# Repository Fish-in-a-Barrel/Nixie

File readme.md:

# Yet Another Nixie Clock

https://github.com/user-attachments/assets/0fcae77a-54a8-4b7d-9e90-6edd31807fbd

## Introduction

This is my Nixie clock project. It was created as an excuse to learn more about electronics and it touches on power circuits, microcontrollers, serial communications, and more.

The clock runs 12 IN-12A Nixie tubes that display the time and date. INS-1 tubes are used for digit separators. It also includes:
- USB-C PD power input
- Boost converter to provide 180V for the nixie tubes
- GPS module for date/time synchronization
- User-selectable timezone
- RTC module for precision timekeeping, and power-off timekeeping
- 128x32 mono OLED display for diagnostics
- Rotary encoder for user input
- I2C Driver boards for each tube

## Development Tools
**Hardware**: KiCad 8
**Firmware**: MPLAB X IDE

## Architecture

### Main Processor
A [Microchip PIC16F15224](https://ww1.microchip.com/downloads/aemDocuments/documents/MCU08/ProductDocuments/DataSheets/PIC16F15213-14-23-24-43-44-Microcontroller-Data-Sheet-40002195.pdf) 8-bit microcontroller is the main processing unit of the clock. It controls the boost converter while managing and coordinating the other hardware modules.

### Power

A [Diodes Incorporated AP33772](https://www.diodes.com/assets/Datasheets/products_inactive_data/AP33772.pdf) is used to negotiate with a PD source for the input power. The AP33772 is controlled by the main MCU via I2C. The AP33772 requests 12V from the power source, which supplies the boost converter.

The AP33772 also provides a dedicated 5V power source. This is a low current source, so it is only used to drive the MCU and UI, which are needed during power-up. A separate 78L05 regulator (powered by the 12V from USB VBUS) provides 5V power to all of the other devices.

Finally, the AP33772 provides over-current and over-voltage protection features.

### User Interface
A 128x32 OLED display (driven by an [SSD1306](https://cdn-shop.adafruit.com/datasheets/SSD1306.pdf)) is used to display status and diagnostics information. A rotary encoder with detent is used to scroll through the different display pages, and to select timezone and DST support. The OLED pixel data is sent over I2C.

### Real Time Clock
A [DS3231](https://www.analog.com/media/en/technical-documentation/data-sheets/ds3231.pdf) RTC module provides an accurate time source for the clock. It is the source of the time/date displayed and is only updated if it differs from the GPS time. The RTC module is also equiped with a battery backup. This allows the clock to display time/date immediately after power-on instead of having to wait several minutes for valid GPS data. RTC data is sent over I2C.

### GPS
The [U-Blox NEO-6M](https://content.u-blox.com/sites/default/files/products/documents/NEO-6_DataSheet_%28GPS.G6-HW-09005%29.pdf) GPS module provides a reference time to initialize the RTC. The module streams standard NMEA messages to the primary MCU over UART serial. Time/date are decoded from these messages.

### Nixie Drivers
Each Nixie tube has a driver board. This board has a [Microchip PIC16F15243](https://ww1.microchip.com/downloads/aemDocuments/documents/MCU08/ProductDocuments/DataSheets/PIC16F15213-14-23-24-43-44-Microcontroller-Data-Sheet-40002195.pdf) MCU in I2C client mode receiving commands from the primary MCU. This client MCU drives the Nixie pins and provides features such as digit cross-fading and cathode maintenance.

## Project Components

### ClockController

This is the main controller board. It connects to a header on the back of the display board and has these main components:
- Primary MCU
- USB PD components
- Boost converter circuitry
- User Interface

### Hardware / Display Board

This board servers as the main support structure of the clock. The Nixie drivers connect to headers on the front of the board. The controller board, GPS, and RTC all connect to the back of the board.

### NixieDriver

The driver board for each individual IN-12 Nixie tube.

### NixieDriverTester

This is a stand-alone test board that will power and exercise a single NixieDriver and tube. It is used for QA of assembled driver boards and testing of the NixieDriver firmware.

### Hardware / Nixie Driver ICSP Adapter

A small board that attaches to a NixieDriver and provides a pin-out compatible with a PICKIT 5 programmer for In Circuit Serial Programming.

### Hardware / Separator

A tiny board that adapts the physical interface of the INS-1 tubes used as digit separators.

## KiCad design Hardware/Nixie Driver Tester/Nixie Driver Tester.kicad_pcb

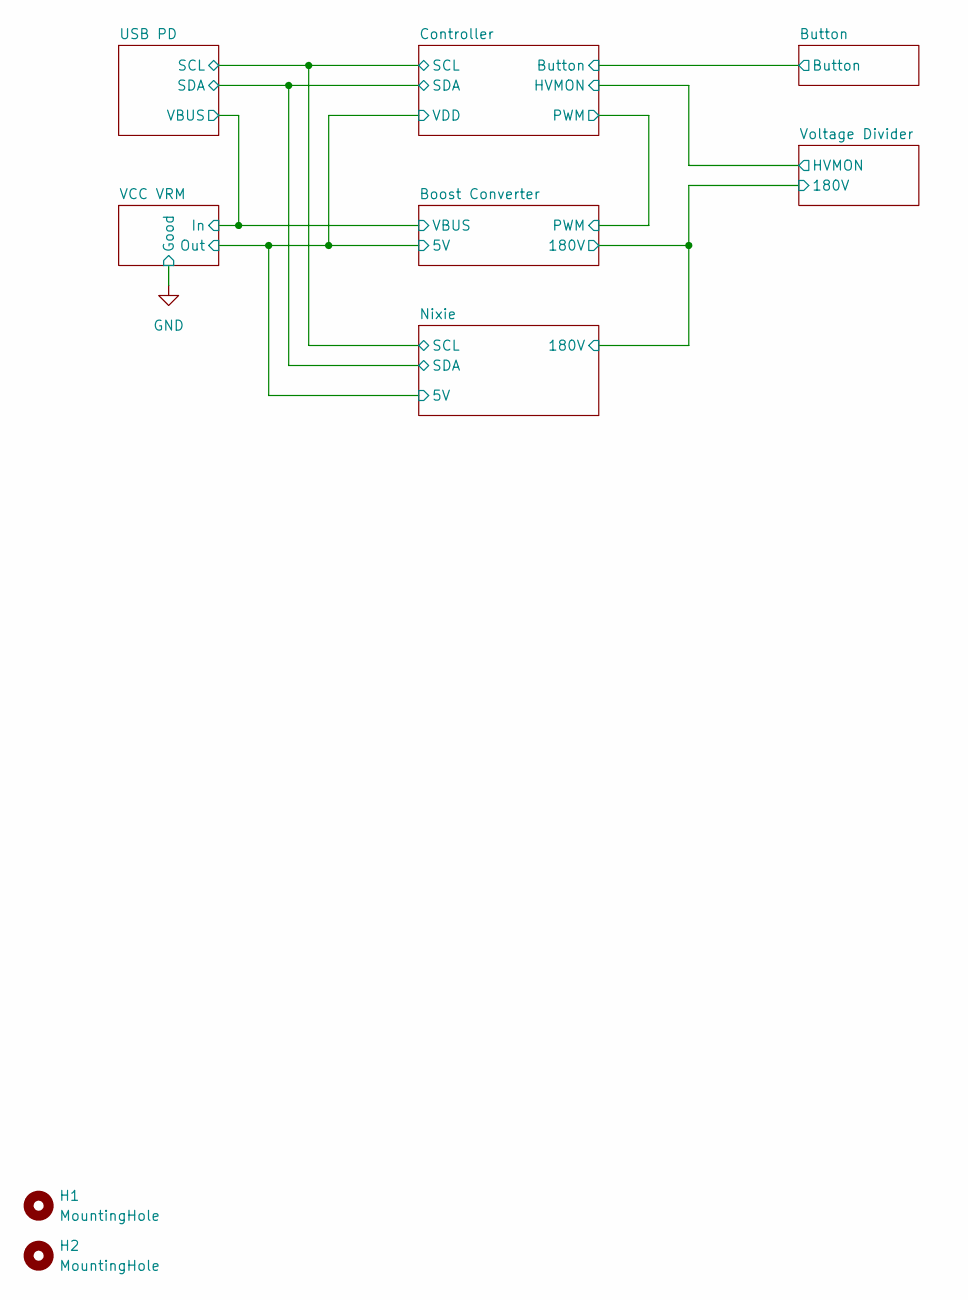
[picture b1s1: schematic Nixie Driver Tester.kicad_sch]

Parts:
H1, H2: MountingHole; MountingHole_3.2mm_M3

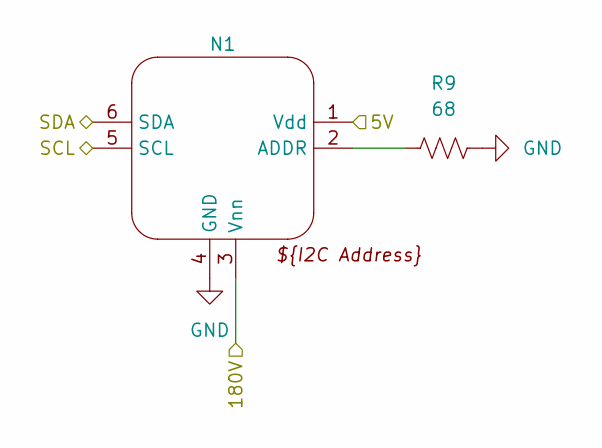
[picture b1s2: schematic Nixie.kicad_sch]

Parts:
N1: Nixie; Nixie Driver V2
R9: 68; R_1206_3216Metric

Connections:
/Boost Converter/180V: N1.3 (Vnn); also elsewhere on the board
/Controller/SCL: N1.5 (SCL); also elsewhere on the board
/Controller/SDA: N1.6 (SDA); also elsewhere on the board
/VCC VRM/V_Out: N1.1 (Vdd); also elsewhere on the board
GND: N1.4 (GND), R9.2; also elsewhere on the board
unnamed: N1.2 (ADDR), R9.1

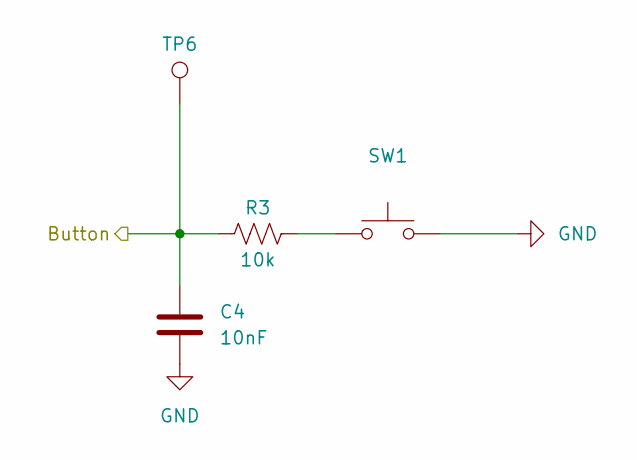
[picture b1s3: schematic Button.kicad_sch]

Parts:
C4: 10nF; C_0603_1608Metric
R3: 10k; R_0603_1608Metric
SW1: SW_Omron_B3FS; B3F-10xx
TP6: BTN; TestPoint_Keystone_5015_Micro_Mini

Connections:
/Button/Button: C4.1, R3.1, TP6.1 (1_1); also elsewhere on the board
GND: C4.2, SW1.2; also elsewhere on the board
unnamed: R3.2, SW1.1

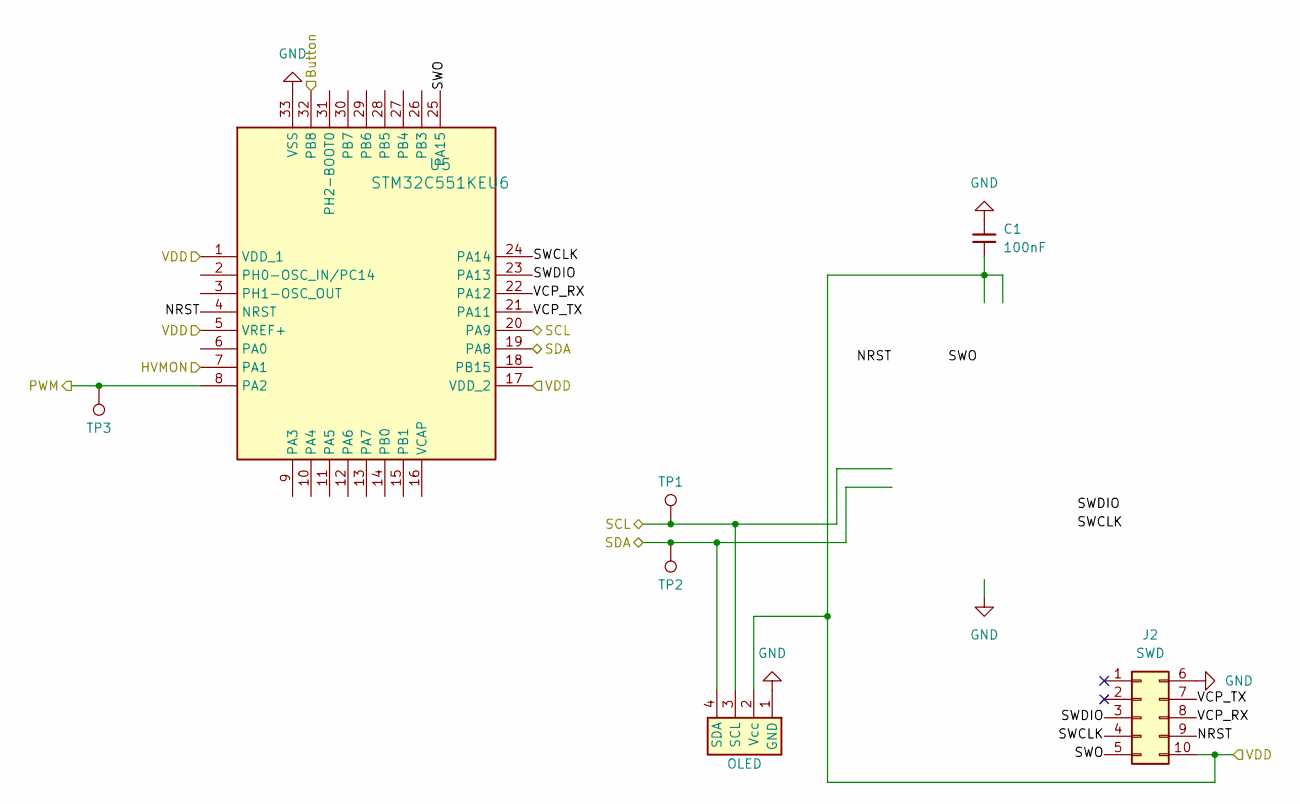
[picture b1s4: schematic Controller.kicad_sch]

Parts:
C1: 100nF; C_0603_1608Metric
J1: OLED; SSD1306 0.91 128x32 OLED
J2: SWD; AVX-009159010061911
TP1: SCL; TestPoint_Keystone_5015_Micro_Mini
TP2: SDA; TestPoint_Keystone_5015_Micro_Mini
TP3: PWM; TestPoint_Keystone_5015_Micro_Mini
U5: STM32C551KEU6; UFQFPN-32-1EP_5x5mm_P0.5mm_EP3.5x3.5mm; Manufacturer_Part_Number STM32C551KEU6

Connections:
/Boost Converter/PWM: TP3.1 (1_1), U5.8 (PA2); also elsewhere on the board
/Button/Button: U5.32 (PB8); also elsewhere on the board
/Controller/HVMON: U5.7 (PA1); also elsewhere on the board
/Controller/NRST: J2.9, U5.4 (NRST)
/Controller/SCL: J1.3 (SCL), TP1.1 (1_1), U5.20 (PA9); also elsewhere on the board
/Controller/SDA: J1.4 (SDA), TP2.1 (1_1), U5.19 (PA8); also elsewhere on the board
/Controller/SWCLK: J2.4, U5.24 (PA14)
/Controller/SWDIO: J2.3, U5.23 (PA13)
/Controller/SWO: J2.5, U5.25 (PA15)
/Controller/VCP_RX: J2.8, U5.22 (PA12)
/Controller/VCP_TX: J2.7, U5.21 (PA11)
/VCC VRM/V_Out: C1.2, J1.2 (Vcc), J2.10, U5.1 (VDD_1), U5.5 (VREF+), U5.17 (VDD_2); also elsewhere on the board
GND: C1.1, J1.1 (GND), J2.6, U5.33 (VSS); also elsewhere on the board

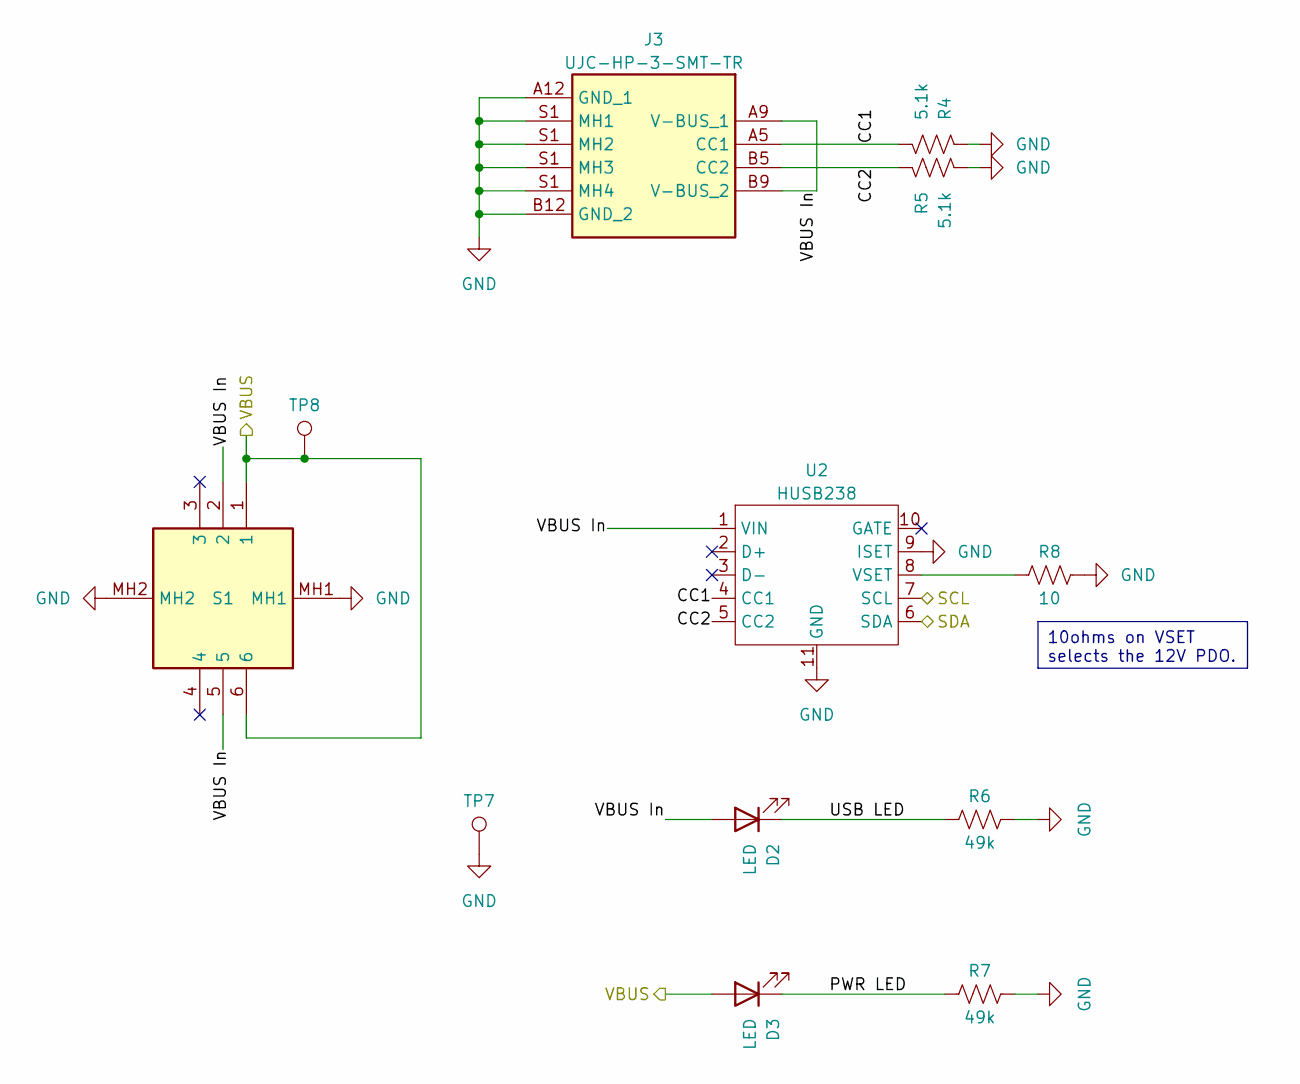
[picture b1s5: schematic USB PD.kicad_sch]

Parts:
D2, D3: LED; LED_0603_1608Metric
J3: UJC-HP-3-SMT-TR; CUI_UJC-HP-3-SMT-TR; Manufacturer_Part_Number UJC-HP-3-SMT-TR; Mouser Part Number 490-UJC-HP-3-SMT-TR
R4, R5: 5.1k; R_0603_1608Metric
R6, R7: 49k; R_0603_1608Metric
R8: 10; R_0603_1608Metric
S1: SLW-111629-7A-D; SLW1116297AD; Mouser Part Number 179-SLW-111629-7A-D
TP7: GND; TestPoint_Keystone_5015_Micro_Mini
TP8: VBUS; TestPoint_Keystone_5015_Micro_Mini
U2: HUSB238; DFN-10-1EP_3x3mm_P0.5mm_EP1.65x2.38mm

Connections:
/Boost Converter/VBUS: D3.2 (A), S1.1, S1.6, TP8.1 (1_1); also elsewhere on the board
/Controller/SCL: U2.7 (SCL); also elsewhere on the board
/Controller/SDA: U2.6 (SDA); also elsewhere on the board
/USB PD/CC1: J3.A5 (CC1), R4.2, U2.4 (CC1)
/USB PD/CC2: J3.B5 (CC2), R5.1, U2.5 (CC2)
/USB PD/PWR LED: D3.1 (K), R7.1
/USB PD/USB LED: D2.1 (K), R6.1
/USB PD/VBUS In: D2.2 (A), J3.A9 (V-BUS_1), J3.B9 (V-BUS_2), S1.2, S1.5, U2.1 (VIN)
GND: J3.A12 (GND_1), J3.B12 (GND_2), J3.S1 (MH3), R4.1, R5.2, R6.2, R7.2, R8.2, S1.MH1, S1.MH2, TP7.1 (1_1), U2.9 (ISET), U2.11 (GND); also elsewhere on the board
unnamed: R8.1, U2.8 (VSET)

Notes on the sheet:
10ohms on VSET selects the 12V PDO.

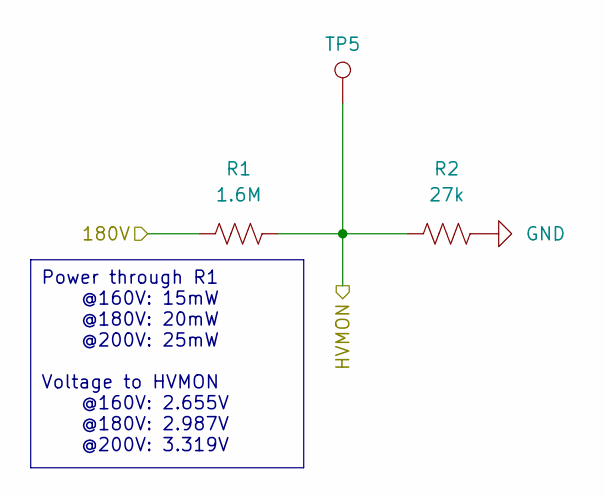
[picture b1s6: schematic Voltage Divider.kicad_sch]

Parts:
R1: 1.6M; R_1206_3216Metric
R2: 27k; R_1206_3216Metric
TP5: MON; TestPoint_Keystone_5015_Micro_Mini

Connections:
/Boost Converter/180V: R1.1; also elsewhere on the board
/Controller/HVMON: R1.2, R2.1, TP5.1 (1_1); also elsewhere on the board
GND: R2.2; also elsewhere on the board

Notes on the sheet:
Power through R1 @160V: 15mW @180V: 20mW @200V: 25mW Voltage to HVMON @160V: 2.655V @180V: 2.987V @200V: 3.319V

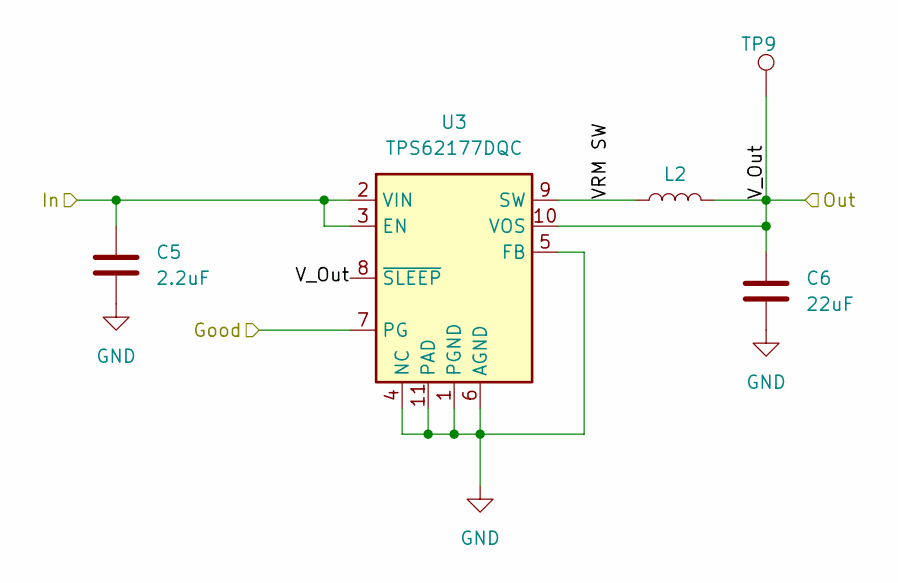
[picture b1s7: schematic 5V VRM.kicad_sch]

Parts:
C5: 2.2uF; C_0805_2012Metric
C6: 22uF; C_0805_2012Metric
L2: VLS4012CX-100M-1; TDK LPS40xx
TP9: 3.3V; TestPoint_Keystone_5015_Micro_Mini
U3: TPS62177DQC; WSON-10-1EP_2x3mm_P0.5mm_EP0.84x2.4mm_ThermalVias

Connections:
/Boost Converter/VBUS: C5.1, U3.2 (VIN), U3.3 (EN); also elsewhere on the board
/VCC VRM/VRM SW: L2.1, U3.9 (SW)
/VCC VRM/V_Out: C6.1, L2.2, TP9.1 (1_1), U3.8 (~SLEEP), U3.10 (VOS); also elsewhere on the board
GND: C5.2, C6.2, U3.1 (PGND), U3.4 (NC), U3.5 (FB), U3.6 (AGND), U3.7 (PG), U3.11 (PAD); also elsewhere on the board

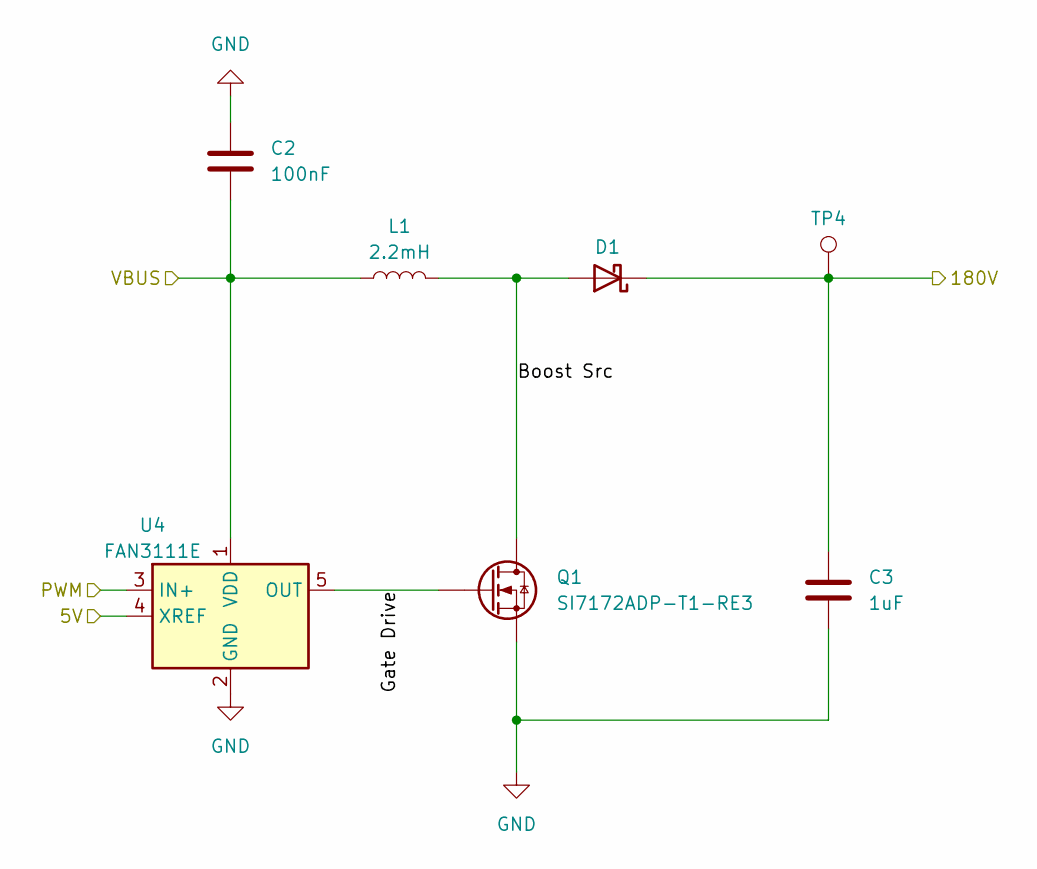
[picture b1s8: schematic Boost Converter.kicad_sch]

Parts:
C2: 100nF; C_0805_2012Metric
C3: 1uF; R_1812_4532Metric
D1: SMD220PL-TP; D_SOD-123
L1: 2.2mH; L_Wuerth_WE-PD-Typ-LS
Q1: SI7172ADP-T1-RE3; PowerPAK_SO-8_Single
TP4: VNN; TestPoint_Keystone_5015_Micro_Mini
U4: FAN3111E; SOT-23-5

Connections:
/Boost Converter/180V: C3.1, D1.1 (K), TP4.1 (1_1); also elsewhere on the board
/Boost Converter/Boost Src: D1.2 (A), L1.2, Q1.D
/Boost Converter/Gate Drive: Q1.G, U4.5 (OUT)
/Boost Converter/PWM: U4.3 (IN+); also elsewhere on the board
/Boost Converter/VBUS: C2.2, L1.1, U4.1 (VDD); also elsewhere on the board
/VCC VRM/V_Out: U4.4 (XREF); also elsewhere on the board
GND: C2.1, C3.2, Q1.S, U4.2 (GND); also elsewhere on the board

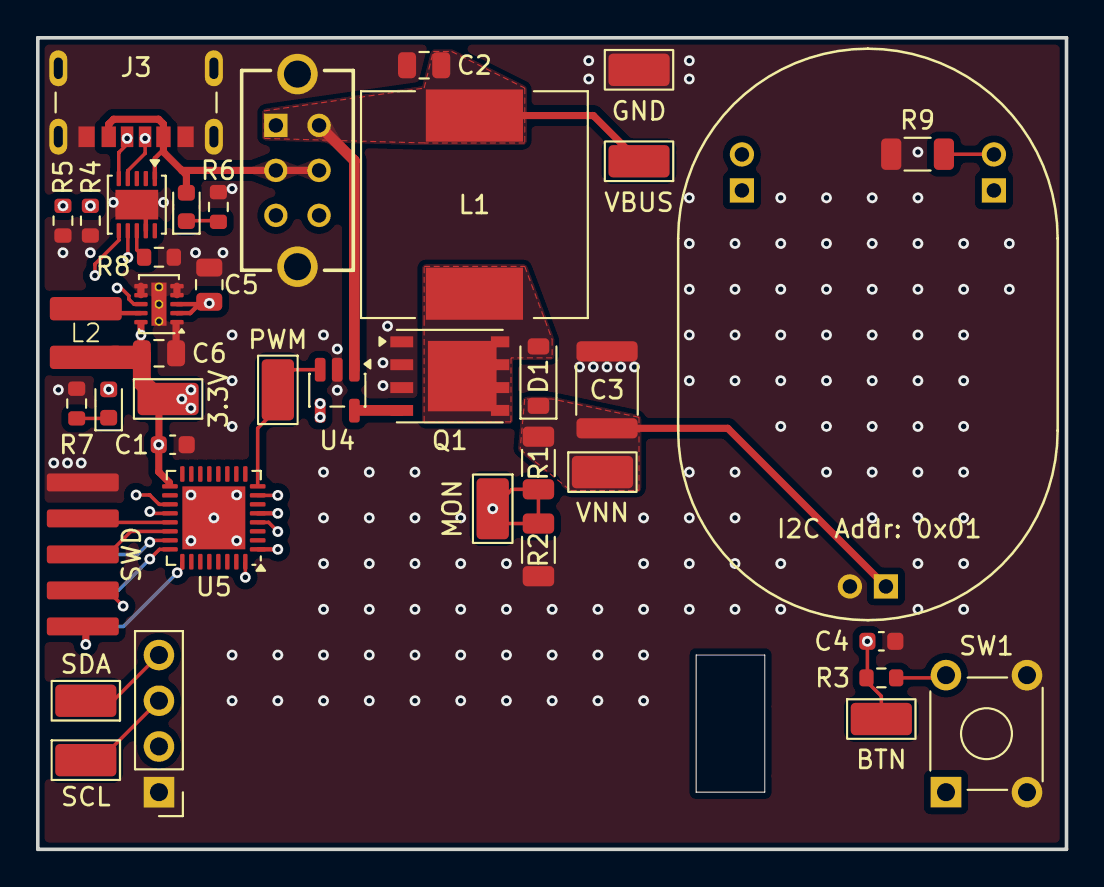
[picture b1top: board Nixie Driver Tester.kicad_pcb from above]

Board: 4 copper layers, 57.1 x 45.1 mm, 42 parts (1 on the bottom side), 26 nets.

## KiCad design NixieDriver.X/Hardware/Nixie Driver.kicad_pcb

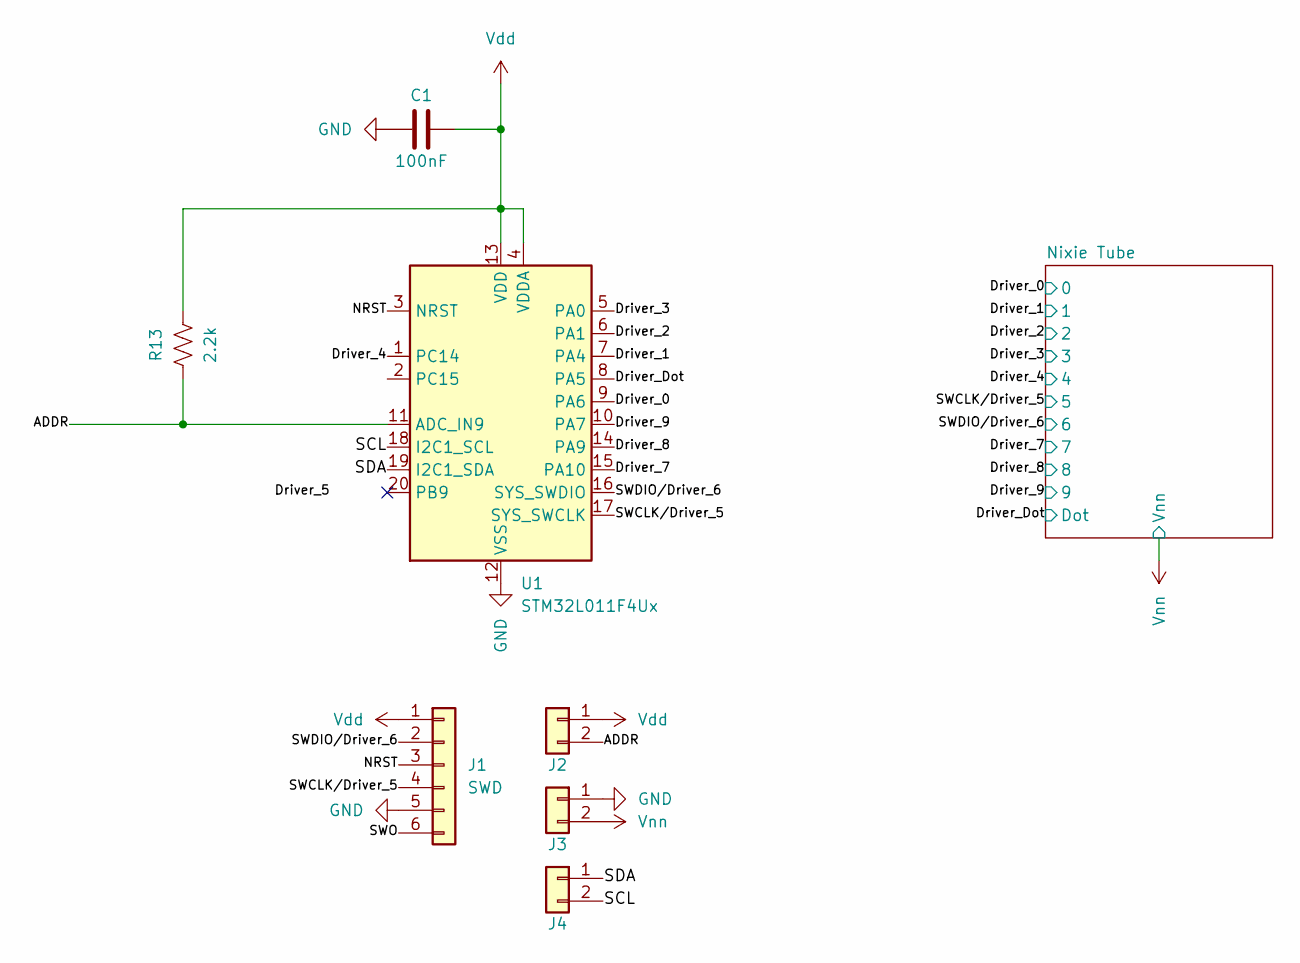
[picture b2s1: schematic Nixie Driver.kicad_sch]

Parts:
C1: 100nF; C_0603_1608Metric
J1: SWD; Tag-Connect EVC3-06
J2, J3, J4: Conn_01x03; PinHeader_1x02_P2.00mm_Vertical
R13: 2.2k; R_0603_1608Metric
U1: STM32L011F4Ux; ST_UFQFPN-20_3x3mm_P0.5mm

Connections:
/ADDR: J2.2, R13.1, U1.11 (ADC_IN9)
/Driver_0: U1.9 (PA6); also elsewhere on the board
/Driver_1: U1.7 (PA4); also elsewhere on the board
/Driver_2: U1.6 (PA1); also elsewhere on the board
/Driver_3: U1.5 (PA0); also elsewhere on the board
/Driver_4: U1.1 (PC14); also elsewhere on the board
/Driver_7: U1.15 (PA10); also elsewhere on the board
/Driver_8: U1.14 (PA9); also elsewhere on the board
/Driver_9: U1.10 (PA7); also elsewhere on the board
/Driver_Dot: U1.8 (PA5); also elsewhere on the board
/NRST: J1.3, U1.3 (NRST)
/SCL: J4.2, U1.18 (I2C1_SCL)
/SDA: J4.1, U1.19 (I2C1_SDA)
/SWCLK/Driver_5: J1.4, U1.17 (SYS_SWCLK); also elsewhere on the board
/SWDIO/Driver_6: J1.2, U1.16 (SYS_SWDIO); also elsewhere on the board
/SWO: J1.6
GND: C1.2, J1.5, J3.1, U1.12 (VSS); also elsewhere on the board
Vdd: C1.1, J1.1, J2.1, R13.2, U1.4 (VDDA), U1.13 (VDD)
Vnn: J3.2; also elsewhere on the board

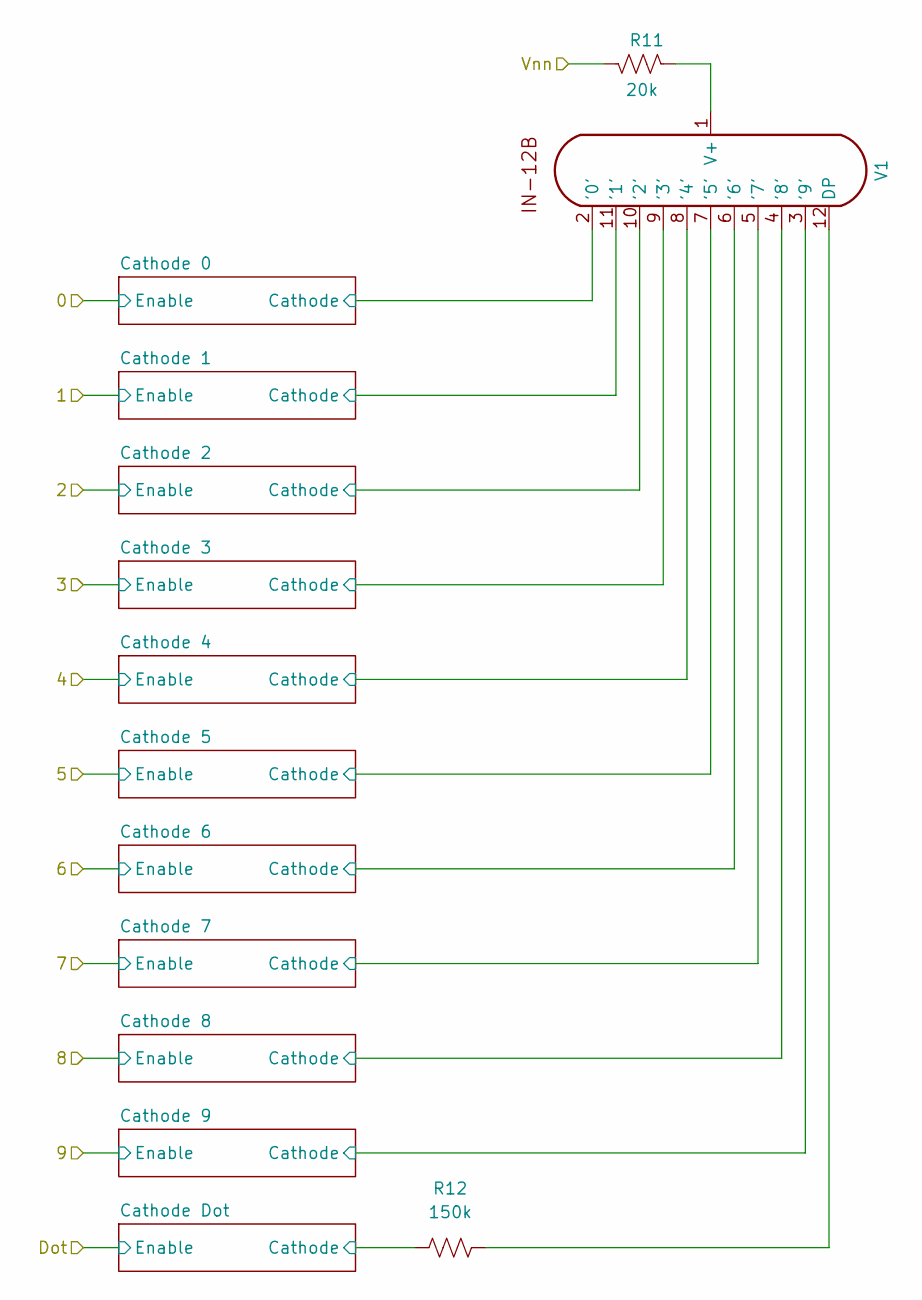
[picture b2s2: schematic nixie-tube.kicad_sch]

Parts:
R11: 20k; R_1206_3216Metric
R12: 150k; R_0805_2012Metric
V1: IN-12B; IN-12[A_B] with center hole

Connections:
/Nixie Tube/Cathode 0/Cathode: V1.2 ('0'); also elsewhere on the board
/Nixie Tube/Cathode 1/Cathode: V1.11 ('1'); also elsewhere on the board
/Nixie Tube/Cathode 2/Cathode: V1.10 ('2'); also elsewhere on the board
/Nixie Tube/Cathode 3/Cathode: V1.9 ('3'); also elsewhere on the board
/Nixie Tube/Cathode 4/Cathode: V1.8 ('4'); also elsewhere on the board
/Nixie Tube/Cathode 5/Cathode: V1.7 ('5'); also elsewhere on the board
/Nixie Tube/Cathode 6/Cathode: V1.6 ('6'); also elsewhere on the board
/Nixie Tube/Cathode 7/Cathode: V1.5 ('7'); also elsewhere on the board
/Nixie Tube/Cathode 8/Cathode: V1.4 ('8'); also elsewhere on the board
/Nixie Tube/Cathode 9/Cathode: V1.3 ('9'); also elsewhere on the board
/Nixie Tube/Cathode Dot/Cathode: R12.1; also elsewhere on the board
unnamed: R12.2, V1.12 (DP)
unnamed: R11.1, V1.1 (V+)
Vnn: R11.2; also elsewhere on the board

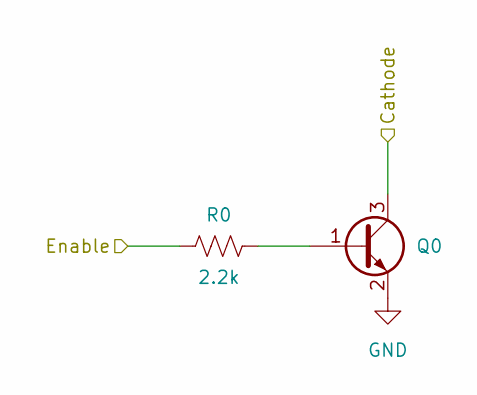
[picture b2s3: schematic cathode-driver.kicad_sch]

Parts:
Q0: MMBTA42LT1G; SOT-23
R0: 2.2k; R_0603_1608Metric

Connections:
/Driver_0: R0.1; also elsewhere on the board
/Nixie Tube/Cathode 0/Cathode: Q0.3 (C); also elsewhere on the board
GND: Q0.2 (E); also elsewhere on the board
unnamed: Q0.1 (B), R0.2

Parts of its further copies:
Q1, Q2, Q3, Q4, Q5, Q6, Q7, Q8, Q9, Q10: MMBTA42LT1G; SOT-23
R1, R2, R3, R4, R5, R6, R7, R8, R9, R10: 2.2k; R_0603_1608Metric

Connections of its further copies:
/Driver_1: R1.1; also elsewhere on the board
/Driver_2: R2.1; also elsewhere on the board
/Driver_3: R3.1; also elsewhere on the board
/Driver_4: R4.1; also elsewhere on the board
/Driver_7: R7.1; also elsewhere on the board
/Driver_8: R8.1; also elsewhere on the board
/Driver_9: R9.1; also elsewhere on the board
/Driver_Dot: R10.1; also elsewhere on the board
/Nixie Tube/Cathode 1/Cathode: Q1.3 (C); also elsewhere on the board
/Nixie Tube/Cathode 2/Cathode: Q2.3 (C); also elsewhere on the board
/Nixie Tube/Cathode 3/Cathode: Q3.3 (C); also elsewhere on the board
/Nixie Tube/Cathode 4/Cathode: Q4.3 (C); also elsewhere on the board
/Nixie Tube/Cathode 5/Cathode: Q5.3 (C); also elsewhere on the board
/Nixie Tube/Cathode 6/Cathode: Q6.3 (C); also elsewhere on the board
/Nixie Tube/Cathode 7/Cathode: Q7.3 (C); also elsewhere on the board
/Nixie Tube/Cathode 8/Cathode: Q8.3 (C); also elsewhere on the board
/Nixie Tube/Cathode 9/Cathode: Q9.3 (C); also elsewhere on the board
/Nixie Tube/Cathode Dot/Cathode: Q10.3 (C); also elsewhere on the board
/SWCLK/Driver_5: R5.1; also elsewhere on the board
/SWDIO/Driver_6: R6.1; also elsewhere on the board
GND: Q1.2 (E), Q2.2 (E), Q3.2 (E), Q4.2 (E), Q5.2 (E), Q6.2 (E), Q7.2 (E), Q8.2 (E), Q9.2 (E), Q10.2 (E); also elsewhere on the board
unnamed: Q1.1 (B), R1.2
unnamed: Q2.1 (B), R2.2
unnamed: Q3.1 (B), R3.2
unnamed: Q4.1 (B), R4.2
unnamed: Q5.1 (B), R5.2
unnamed: Q6.1 (B), R6.2
unnamed: Q7.1 (B), R7.2
unnamed: Q8.1 (B), R8.2
unnamed: Q9.1 (B), R9.2
unnamed: Q10.1 (B), R10.2

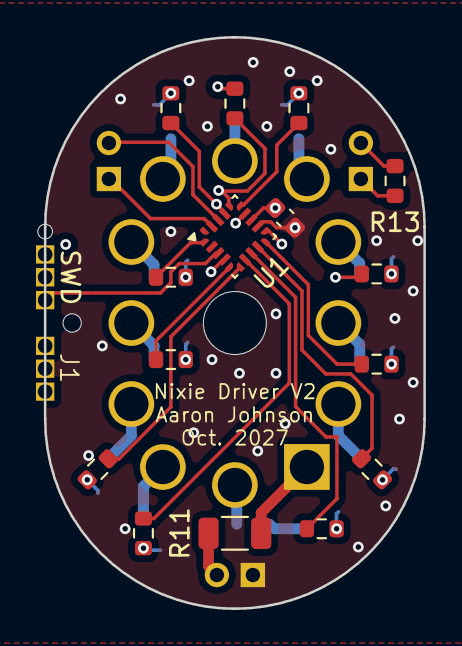
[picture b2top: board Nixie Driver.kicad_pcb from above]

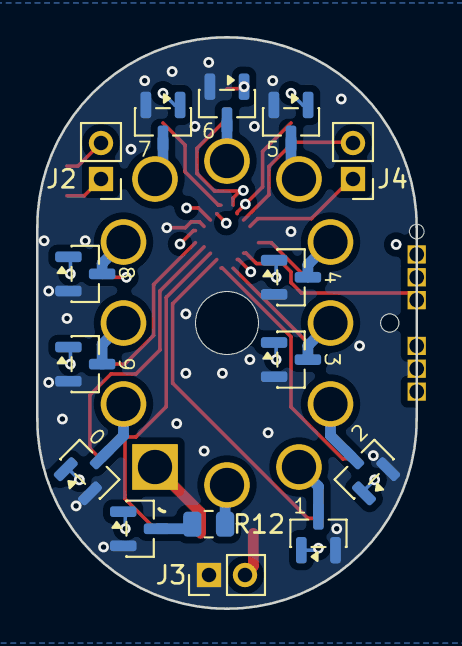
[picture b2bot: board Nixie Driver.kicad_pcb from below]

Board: 4 copper layers, 21.1 x 31.8 mm, 32 parts (16 on the bottom side), 42 nets.

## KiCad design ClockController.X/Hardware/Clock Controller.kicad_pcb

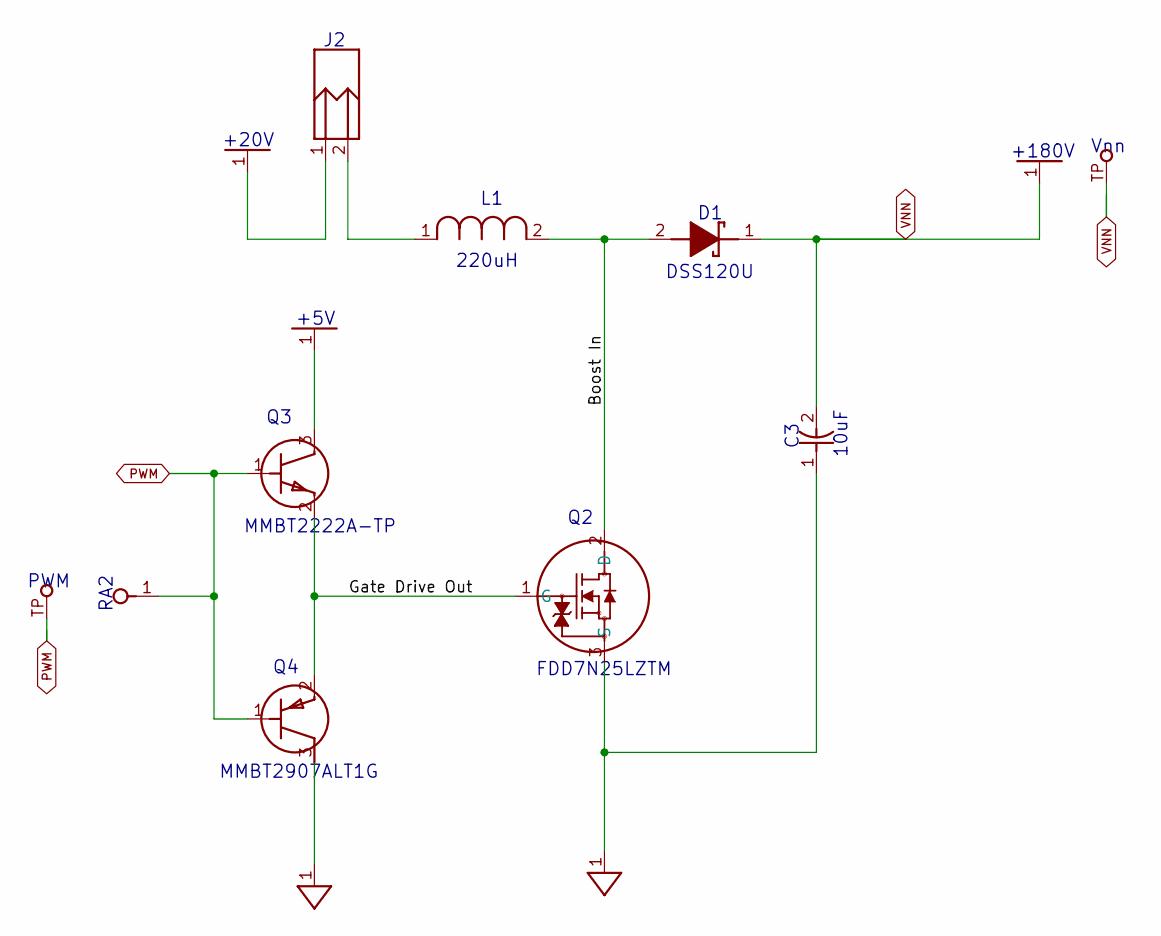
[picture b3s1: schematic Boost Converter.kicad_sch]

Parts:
C3: 10uF; C_1812_4532Metric
D1: SMD220PL; D_SOD-123F
J2: HDR-1X2H; PinHeader_1x02_P2.54mm_Horizontal
L1: 220uH; SRN8040TA221M
PWM0: Most Density; TP_1.25MM
Q2: FDD7N25LZTM; TO-252-2
Q3: MMBT2222A-TP; SOT-23
Q4: MMBT2907ALT1G; SOT-23
Vnn0: Most Density; TP_1.25MM

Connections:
+5V: Q3.3 (C); also elsewhere on the board
+20V: J2.1; also elsewhere on the board
/Boost Converter/Boost In: D1.2 (A), L1.2, Q2.2 (D)
/Boost Converter/Gate Drive Out: Q2.1 (G), Q3.2 (E), Q4.2 (E)
GND: C3.1, Q2.3 (S), Q4.3 (C); also elsewhere on the board
unnamed: J2.2, L1.1
PWM: PWM0.TP, Q3.1 (B), Q4.1 (B); also elsewhere on the board
VNN: C3.2, D1.1 (K), Vnn0.TP; also elsewhere on the board

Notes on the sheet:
MMBT2222A-TP
FDD7N25LZTM
+180V
PWM
DSS120U
Vnn
RA2
MMBT2907ALT1G
220uH
+5V
+20V
10uF

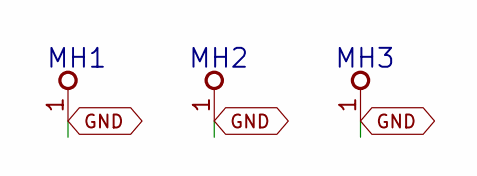
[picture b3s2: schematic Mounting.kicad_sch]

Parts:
MH1, MH2, MH3: M2.5_MTGP540H285

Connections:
GND: MH1.1, MH2.1, MH3.1; also elsewhere on the board

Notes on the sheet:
MH1
MH3
MH2

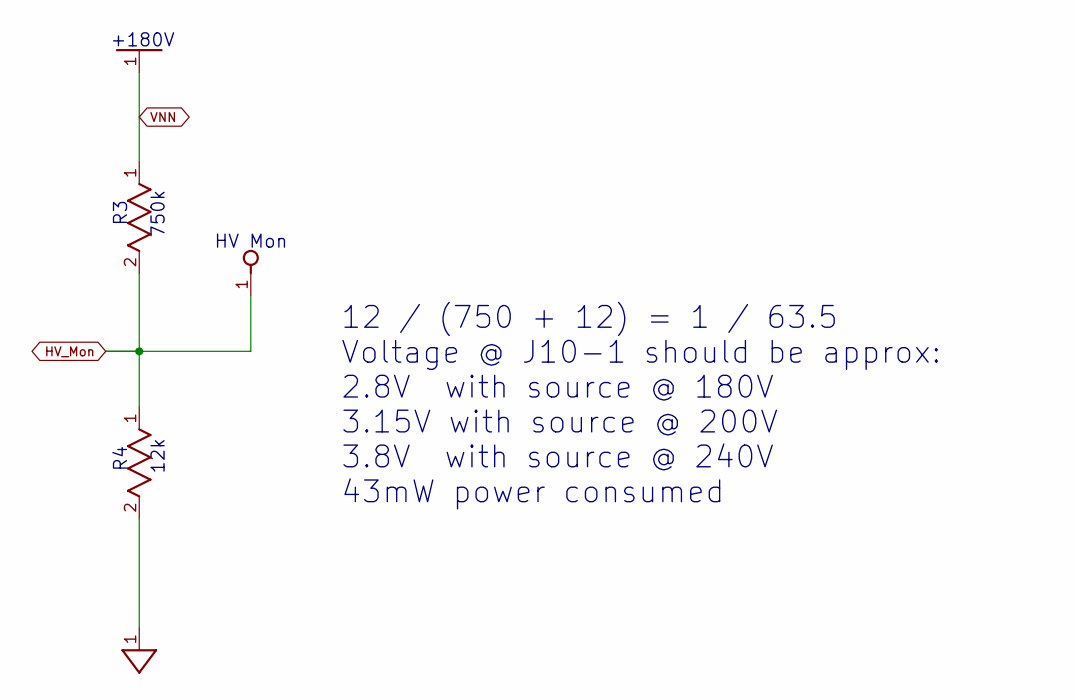
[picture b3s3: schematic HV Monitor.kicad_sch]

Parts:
R3: 750k; R_0805_2012Metric
R4: 12k; R_0805_2012Metric

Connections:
GND: R4.2; also elsewhere on the board
HV_Mon: R3.2, R4.1; also elsewhere on the board
VNN: R3.1; also elsewhere on the board

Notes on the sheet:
12 / (750 + 12) = 1 / 63.5 Voltage @ J10-1 should be approx: 2.8V with source @ 180V 3.15V with source @ 200V 3.8V with source @ 240V 43mW power consumed
+180V
HV Mon
12k
750k

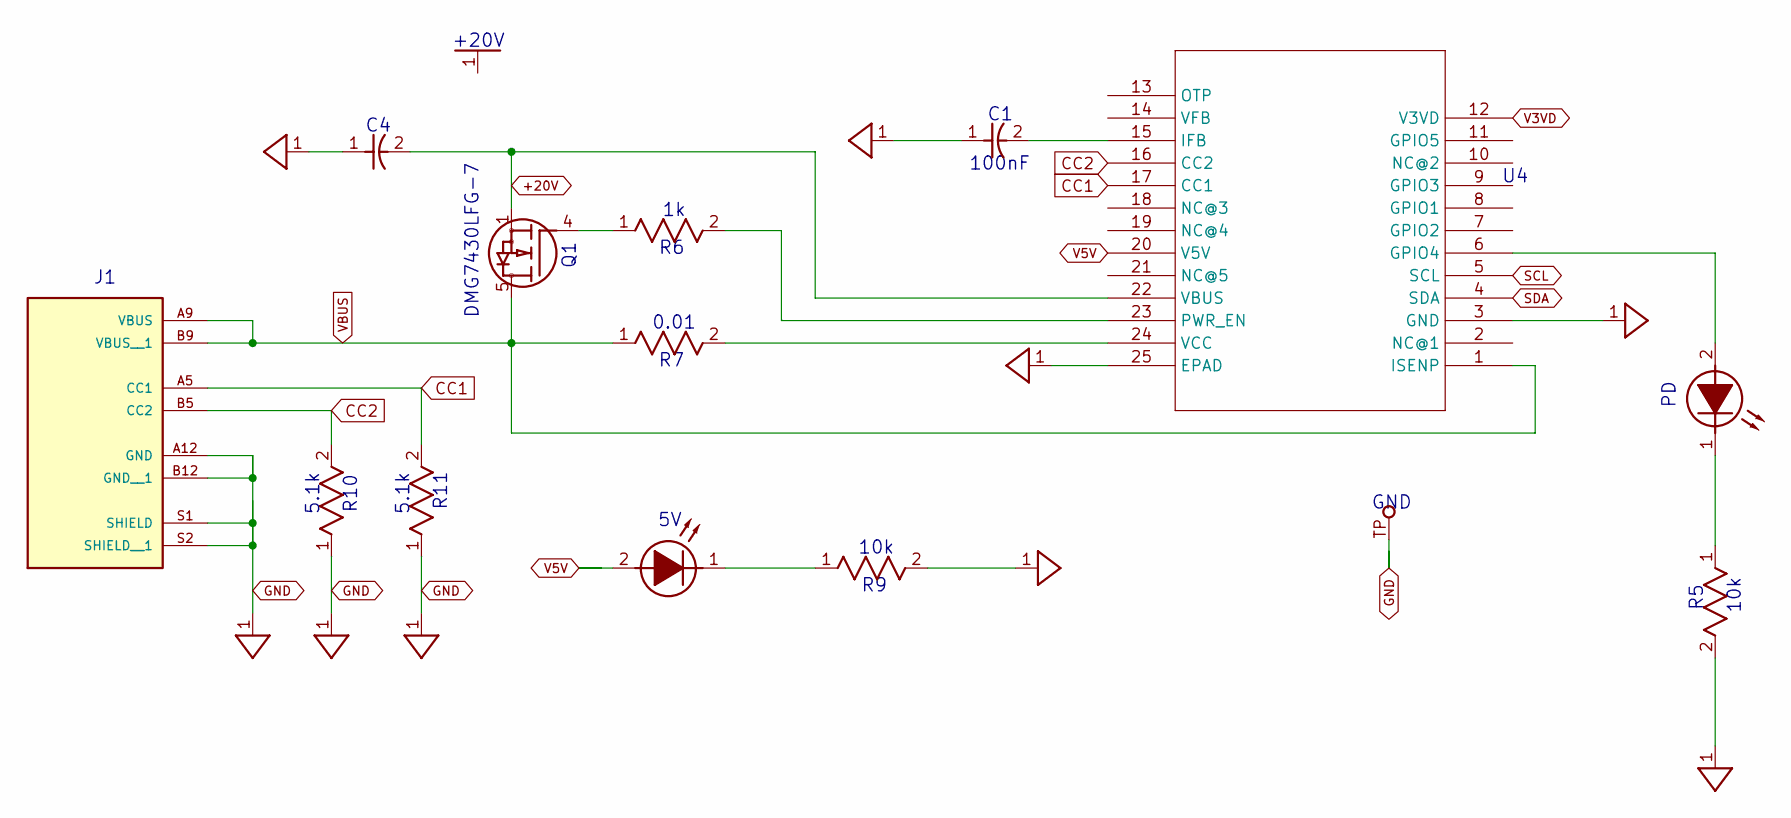
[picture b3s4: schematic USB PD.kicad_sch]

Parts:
C1: 100nF; C_0805_2012Metric
C4: 1uF; C_1206_3216Metric
GND0: Most Density; TP_1.25MM
J1: UJC-VP-3-SMT-TR; CUI_UJC-VP-3-SMT-TR; PARTREV 1.0
PD0: LED_1206(3216_METRIC)_N_BLUE; LED_1206_3216Metric
Q1: DMG7430LFG-7; PowerDI3333-8
R5, R9: 10k; R_0603_1608Metric
R6: 1k; R_0805_2012Metric
R7: 0.01; R_1206_3216Metric
R10, R11: 5.1k; R_0603_1608Metric
U4: AP33772DKZ-13; QFN-24-1EP_4x4mm_P0.5mm_EP2.7x2.7mm
UNK5V0: LED_1206(3216_METRIC)_N_GREEN; LED_1206_3216Metric

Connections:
+20V: C4.2, Q1.1 (S), Q1.2 (S), Q1.3 (S), U4.22 (VBUS); also elsewhere on the board
CC1: J1.A5 (CC1), R11.2, U4.17 (CC1)
CC2: J1.B5 (CC2), R10.2, U4.16 (CC2)
GND: C1.1, C4.1, GND0.TP, J1.A12 (GND), J1.B12 (GND__1), J1.S1 (SHIELD), J1.S2 (SHIELD__1), R5.2, R9.2, R10.1, R11.1, U4.3 (GND), U4.25 (EPAD); also elsewhere on the board
unnamed: PD0.2 (A), U4.6 (GPIO4)
unnamed: PD0.1 (K), R5.1
unnamed: Q1.4 (G), R6.1
unnamed: C1.2, U4.15 (IFB)
unnamed: R6.2, U4.23 (PWR_EN)
unnamed: R7.2, U4.24 (VCC)
unnamed: R9.1, UNK5V0.1 (K)
SCL: U4.5 (SCL); also elsewhere on the board
SDA: U4.4 (SDA); also elsewhere on the board
V3VD: U4.12 (V3VD)
V5V: U4.20 (V5V), UNK5V0.2 (A); also elsewhere on the board
VBUS: J1.A9 (VBUS), J1.B9 (VBUS__1), Q1.5 (D), Q1.6 (D), Q1.7 (D), Q1.8 (D), R7.1, U4.1 (ISENP)

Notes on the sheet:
0.01
R10
10k
+20V
5.1k
R11
GND
100nF
DMG7430LFG-7
